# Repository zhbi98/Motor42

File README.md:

# Motor42

转速-扭矩特性步进电机运用普通的开环控制方式在低速和低负载的情况下可以保持较好的控制精度，但随着负载增大或转速度增加会发生丢步，另一个是转速-扭矩特性让步进电机无法在高转速下稳定工作。

## 特性

在低速状态下，步进电机的扭矩特性曲线通常为水平直线，能够提供较高的扭矩。在高速状态下，由于电感的影响，扭矩特性曲线呈指数下降，导致电机的负载能力显著降低。

> **最大扭矩：** 最大扭矩出现在中低转速范围，随着转速的提高，扭矩会逐渐下降。因为在高频率下，电流流动受到绕组电感的影响，导致电流无法达到稳定值，从而扭矩降低。
> 
> **启动扭矩与连续扭矩：** 启动扭矩指在启动时能够提供的最大扭矩，而连续扭矩则指电机持续运行时能够维持的扭矩。随着脉冲频率的增加，启动扭矩和连续扭矩都会下降。

## 闭环

闭环控制是在开环控制的基础上，增加了 **反馈检测环节**（例如在电机轴增加编码器），形成指令-执行-位置检测-修正的闭环逻辑。解决存在的丢步、偏差、抗干扰能力弱问题，还能提升系统和容错能力。

## FOC 控制

混合式步进电机与无刷电机的内在联系（结构定义相似性，工作原理相似性），所以可以用无刷电机 FOC 的驱动思想驱动步进电机。

结构方面：永磁转子+定子绕组的结构，定子方面：两者都有多相绕组（步进电机通常为两相，无刷电机通常为三相），转子方面：都采用永磁材料制造转子磁极，无刷设计：两者都没有电刷和机械换向器，依靠电子换向。

对于两相步进电机，虽然只有两个绕组，但通常两相绕组是正交的，从而可以简化步骤，省略我们的 clarke 变换，所以其余同样可以采用类似的思路进行一个电流环FOC控制。

    电流检测：对 AB 两相电流进行检测
    Park变换：将 AB 轴静止系转换为dq轴旋转坐标系
    PI调节器：对 Id 和 Iq 进行控制
    Invpark变换：讲 dq 轴转换为AB轴
    SVPWM调制: 输出占空比
    双 H桥驱动：驱动我们的步进电机

这些可以整合到一个驱动器中实现，如下图。这就是一体化集成步进电机闭环驱动器。板上集成磁编码器，具有速度，位置，电流闭环控制功能，适用于 3D 打印机，小型机械臂。

## 硬件

(1) 2 相逆变功率级：东芝凌耐压 50V，载流3.5A 的 PWM 斩波式双全桥电机驱动器，内置带低导通电阻的输出MOSFET（基于成本考虑可以选择其他的型号）。

(2) RS485 收发器：TI 德州仪器 SN75176B（基于成本考虑可以选择其他的型号）。

(3) CAN2.0B 收发器：NXP 恩智浦 High-speed CAN transceiver TJA1051（基于成本考虑可以选择其他的型号）。

(4) 磁编码器：MagnTek 麦歌恩 mt6816 单圈绝对式14位编码器，支持最高转速25Krpm。

(6) 主控 MUC 芯片：意法半导体 STM32F103。

## 关于打样

驱动器板 Motor42（PCB 采用?**4 层板**?设计）：[HardWare/kiacd_project](./HardWare/kiacd_project)

如果想自己修改 PCB 需要安装 KiCad（开源的 EDA 工具，也非常易学），官方下载地址： https://www.kicad.org/。

打样制作可以直接进入到下面这两个路径下：

把 Motor42 Gerber 文件夹 [HardWare/Gerber](./Docs/Motor42-PCB/) 压缩为 Motor42.zip，

把这个 .zip 给 PCB 制造厂即可（例如 JLC，**PCB 经过打样验证，可以放心使用**）。

**器件 BOM 目录**：[HardWare/ibom.html](./Docs/Motor42-BOM.csv)（PCB 没器件位号，按网页交互式 BOM 贴片）。

原理图 PDF 目录： [Docs/Motor42-SCH.csv](Docs/Motor42-SCH.pdf)

## 核心固件

固件主要包括几大功能模块：

- hal 驱动：板载的各种硬件驱动比如 USB、Tim、Can、Spi。
- utils 库：STM32 的 Flash 存储接口，Modbus 协议解析库，软定时器组件。
- drivers：ARM的CMSIS驱动，ST官方的HAL库。
- device：电机H桥驱动，编码器驱动和校准，电机控制核心代码，LED 驱动框架 LedMX 和按键驱动 MultiButton。
- main：上层 Can，Rs485 应用控制协议，用于控制同步电机状态/参数，以及用户设置参数保存功能。

## 编译下载

固件没有使用 ARM Keil 开发，而是先用 CMake 构建出 Makefile，然后再用 arm-gcc 编译（可以自己创建 F103 的 Keil 工程，把 Motor42 组织到 Keil 编译）。

Motor42 用的是 VSCode 搭配 OpenOCD 图形化下载调试，需要下载安装下列工具链：

MiniGW： https://sourceforge.net/projects/mingw-w64/files/

arm-gcc ：[Downloads | GNU Arm Embedded Toolchain Downloads – Arm Developer](https://developer.arm.com/downloads/-/gnu-rm)

openOCD：[Download OpenOCD for Windows](https://gnutoolchains.com/arm-eabi/openocd/)

CMake：[Download CMake](https://cmake.org/download/)

VSCode：[https://code.visualstudio.com/](https://code.visualstudio.com/)

> 安装后具体如何配置使用这些工具，篇幅较长不写在这里，我把具体配置使用方法写在这里：[工具链配置使用方法](https://blog.csdn.net/jf_52001760/article/details/126826393)。

**Motor42 编译步骤**：

把 cmake 脚本 CMakeLists.txt 的目录添加到 `1` 这里，如下图。

(2) 在 Firmware 目录下创建 build 目录，并指定到 `2` 这里。

(3) 点击 "Configure"，在弹出面板选择目标工程，如下图。

(5) 在 vscode 的命令行 `cd build` 进入`build/`目录，然后执行 make -j2 即可开始编译。

(6) 使用 openOCD 把 `.elf` 文件下载到 Motor42 硬件，下载方法同样参照 [工具链配置使用方法](https://blog.csdn.net/jf_52001760/article/details/126826393)（PCB 上预留了 SWD 调试接口同时支持固件下载）。

## 电机选型

电机可以在淘宝搜索购买，最好购买低相电阻步进电机（较好的电机的相电阻通常为 2-5 Ohm）。相电阻过高可能导致电机在静止时出现高频震动。

电机机身：34MM，出轴直径：5MM (D轴4.5MM)，出轴长度：22MM
静力矩：0.29 N.m，额定电流：1.5 A，电阻：3.0Ohm/相。

> 要实际测量电机相电阻（万用表接到对应相的两个端子测量），比如购买的步进电机在参数描述中标明的相电阻为 2.2 Ohm，实则实际测出的相电阻高达 29 Ohm
> 
> 

## 编码器安装

在电机轴上安装径向磁铁（用于磁编码器检测），磁铁尺寸?$d=8mm$，$h=2mm$，注意径向磁铁和轴同心度不要过度偏移，让后把驱动器板放到板支架中，用 M3.0 螺丝把驱动器和板定到电机尾部，磁铁与编码器的间隙大概为 $1mm$。

驱动板支架零件目录：[Model](./Model)，把 .step 文件给 3D 打印即可。

## Configuration

固件上已经调试好 Pid 参数，可以适配大多数42步进电机，默认情况下不需要再调试 Pid 电机也能正常工作。Pid 可以用 Can 指令调整（看Can协议部分的说明），方法如下：

- **Kp 的调整**：将 Kd，Ki 置 0，从零开始逐渐增加 Kp，直到系统出现震荡。然后逐渐减小Kp，直到系统不再震荡。Kp 的最终值通常在引起震荡的 Kp 值的 80%-90% 之间。

- **Kd 的调整**：在 Kp 调整稳定后，开始增加 Kd。如果系统在空载时仅需要 Kp，那么在负载情况下可能需要增加 Kd 来减少超调和震荡。

- **Ki 的调整**：如果系统在 Kp 和 Kd 的调整后仍然存在静态误差，可以尝试增加 Ki。但 Ki的值通常很小，需要细致地调整。

配置限制参数，限制参数再 /motor/control_config.h 文件定义，如下。

```c
/********************  硬件配置区  ********************/
#define _Current_Rated_Current  (3000)  /**< 额定电流(mA)*/
#define _Current_Cali_Current   (2000)  /**< 校准电流(mA)*/
/********************  运动参数配置区  ********************/
...
#define _Move_Rated_Speed           ((int32_t)(50 * Move_Pulse_NUM))    /**< (额定转速)(50转每秒)*/
#define _Move_Rated_UpAcc           ((int32_t)(1000 * Move_Pulse_NUM))  /**< (固件额定加速加速度)(1000r/ss)*/
#define _Move_Rated_DownAcc         ((int32_t)(1000 * Move_Pulse_NUM))  /**(固件额定减速加速度)(1000r/ss)*/
#define _Move_Rated_UpCurrentRate   ((int32_t)(20 * _Current_Rated_Current))    /**< (固件额定增流梯度)(20倍额定/s)*/
#define _Move_Rated_DownCurrentRate ((int32_t)(20 * _Current_Rated_Current))    /**< (固件额定减流梯度)(20倍额定/s)*/
```

用户设置在 /main/setup/setup.c 中定义，用户设置参数可以用 Can 指令设置（看Can协议部分的说明）设置后保存在 Flash 掉电保存。

```c
const _setup_t _setup_def = {
    ...
    .can_id = 0x01,
    .home_ofs = 0,
    ...
    .current_down_acc = 2 * 1000, /*(mA/s)*/
    .current_up_acc = 2 * 1000, /*(mA/s)*/
    .current_rated = 1000,
    .cali_current = 2000,
    ...
};
```

## 按键逻辑

(1) 启动停止闭环模式：按键 1 短按一次，启动或停止闭环模式，启动闭环模式的同时会进入默认的模式，例如位置闭环。

(2) 目标清 0：按键 2 短按一次，如果当前控制模式为速度模式，那么按下此时会将目标速度置为 0，位置模式，则将目标位置置为 0。

(3) 电机编码器校准：按键 1 长按两次，校准时电机会慢速正转一圈再反转一圈。

> 按下按键时 LED 跟随闪烁，以指示按键是否响应。

## 通信协议

驱动器支持 RS485+Modbus 和 CAN 协议。

### CAN 协议

一帧 CAN 报文只能传 8 个字节数据，和 11 位的标准 Std-Id，这里把 Std-Id 的低 7 位也用作数据，用来传控制指令字 CMD，控制协议定义如下：

Device Id 占用 4 位，CMD 占用 7 位，协议最多两个参数：参数 1 占用 4 个字节，参数 2 占用 4 个字节。

> 个别协议要两个参数，例如位置控制：设置目标位置和速度限制。

具体指令在[protocols/can_protocol.c](./Firmware/main/protocols/can_protocol.c) 这里定义，具体可以看这个文件，具体控制指令和控制方式查看 [Docs/Protocols](./Docs/Protocols) 目录下相应的协议文档，这里只截取部分。

### Rs485 协议

具体控制指令和控制方式查看 [Docs/Protocols](./Docs/Protocols) 目录下相应的协议文档，这里只截取部分。

## 震动问题

注意步进驱动器控制步进电机工作在位置环并要求静止在某个固定位置时可能会出现高频震动的问题。引起高频微弱震动的原因是由于在位置环控制模式下，驱动器为了让让电机接近指定位置而控制电机在齿槽间反复微调而产生震动。

> 这个现象排除驱动器的电路问题（比如焊接的电流采样电阻是否正确等等），磁编码器检测磁铁的安装同心度问题（通常同心度要求不是很高，确保不要过度偏移即可）那有极大的可能是步进电机的相电阻过大导致的，可以更换了其他电机进行测试。

如果更换电机测试后发现同一个闭环步进电机驱动器驱动一个步进电机工作在位置环保持静止时工作正常，而驱动另一个步进电机静止时出现高频震动，那可以肯定就是相电阻过高而导致的。出现震动现象的电机相电阻通常为 10-30 Ohm，而较好电机的相电阻通常为 2-5 Ohm。注意检查电机参数可能的虚标，例如购买的步进电机在参数描述中标明的相电阻为 2.2 Ohm，实则实际测出的相电阻高达 29 Ohm，所以电机出现震动现象和线圈相电阻是有一定关系的。

可以通过修改驱动器程序固件来修复这个问题，修改驱动输出部分，在最终 FOC 输出驱动电流部分添加一个系数即可，通过该系数来调节驱动器 FOC 的输出电流（当然调节电流参数会对最终的扭矩有略微的影响，但并不影响闭环精度），如下图。

## 控制带宽

电机控制速度/位置积分需要精确节拍，电机控制所有逻辑都是在定时器触发的中断中进行，我设置的中断函数频率较高，达到20KHz，可能会导致 main 主循环不执行。

> **20 kHz 中断**：TIM 每 50 μs 触发一次中断。

**电机控制逻辑较多：** 运行时间合计接近或超过 50 μs，会形成中断几乎连轴转、主循环几乎没机会跑”的情况（和芯片主频无关，只要中断内处理的时间超过中断周期时间就会导致 main 函数不执行）。

> 通过 SPI 阻塞读 MT6816，最多 3 次尝试 × 2 次 16bit 传输，再加 16 位奇偶校验循环。SPI 时钟为 9MHz，仅通信就可能 5-15μs。
> 
> 编码器处理、位置/速度估计、多种运行模式下的控制（DCE/PID/电流等）、运动规划、软目标更新、堵转/过载检测等就需要数十μs。

没有具体要求需要多少控制频率，控制制带宽越高，控制越平滑所以默认设定为 20KHz，若控制带宽允许，可把闭环控制改为 10 kHz 或 5 kHz，中断周期变为 100 μs / 200 μs。

> 这里 20 kHz 不是控制带宽的硬性要求，更多是裕量和步进分辨率。

修改控制频率同时改两处：
motion_planner.h 的  CONTROL_FREQUENCY 定义。
修改电机控制运行中断定时器的中断时间。

```c
/****************************************  控制器频率配置区  ****************************************/
#define CONTROL_FREQ_HZ   (20000)                     /**< 控制频率_hz*/
#define CONTROL_PERIOD_US (1000000 / CONTROL_FREQ_HZ) /**< 控制周期_us*/
```

### 评估控制带宽

(1) motor.cpp 涉及的一阶滤波：由 `等效时间常数由 >> 5`（约 32 个采样）决定。20 kHz 时：32 × 50us =1.6 ms 即控制带宽约 100 Hz。对很多应用来说 50 Hz 左右就足够。

(2) 位置/速度环 (DCE、PID 闭环带宽)：这是外环（位置环、速度环），一般做到几十到一两百 Hz 带宽就足够（位置/速度环 -3 dB 带宽）。 

> 常见经验：**采样率 ≥ 10～20 倍闭环带宽**。 
> 若你目标闭环带宽在 100～200 Hz，**5 kHz 已经够用，2 kHz 是底线**。

(3) FOC/电流指令：由 TB67H450 等驱动接收，5～10 kHz 更新电流给定对多数应用足够。

(4) 运动规划：用 CONTROL_FREQUENCY 做离散积分，频率高一点更平滑，但 5～10 kHz 通常足够平滑。

(5) 控制更新频率：下限约 2～5 kHz（再低速度估计和环路的相位裕量会变差）。推荐 5～10 kHz 在保证控制性能的同时，能给主循环留出明显时间。在需要 **极高步进率** 或 **尽量小的相位延迟** 时才必要 20 kHz。

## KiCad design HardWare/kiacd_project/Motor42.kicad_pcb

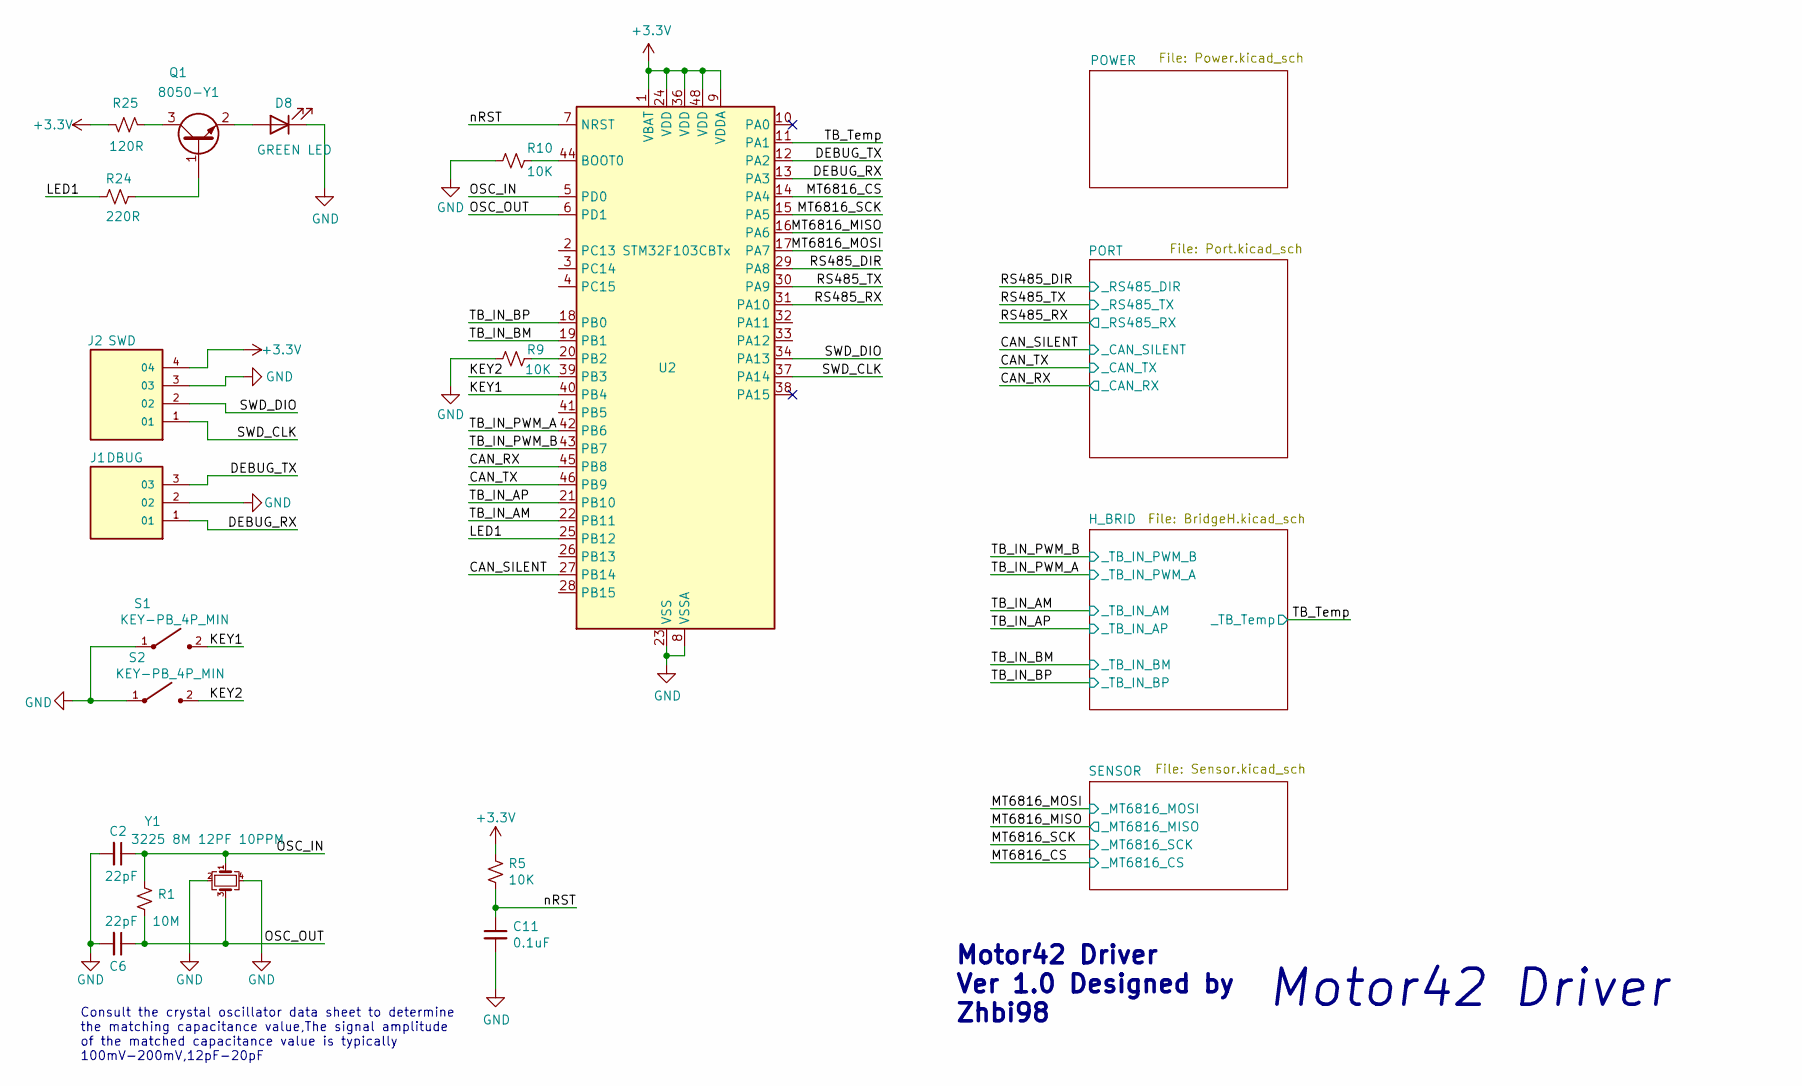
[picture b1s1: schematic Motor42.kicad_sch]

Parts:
C2, C6: 22pF; C_0603_1608Metric
C11: 0.1uF; C_0603_1608Metric
D8: GREEN LED; LED_0603_1608Metric
J1: DBUG; CONN-SMD_1x3P-P1.0-H_WAFER-SH1.0-3PWB
J2: SWD; CONN-SMD_1x4P-P1.0-H_WAFER-SH1.0-4PWB
Q1: 8050-Y1; SOT-23
R1: 10M; R_0603_1608Metric
R5, R9, R10: 10K; R_0603_1608Metric
R24: 220R; R_0603_1608Metric
R25: 120R; R_0603_1608Metric
S1, S2: KEY-PB_4P_MIN; KEY-SMD_2P_L4.0-W3.0-V_K2-1807SN-A3DW-06
U2: STM32F103CBTx; LQFP-48_7x7mm_P0.5mm
Y1: 3225 8M 12PF 10PPM; Crystal_SMD_3225-4Pin_3.2x2.5mm

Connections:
+3.3V: J2.4, R5.1, R25.1, U2.1 (VBAT), U2.9 (VDDA), U2.24 (VDD), U2.36 (VDD), U2.48 (VDD); also elsewhere on the board
/CAN_RX: U2.45 (PB8); also elsewhere on the board
/CAN_SILENT: U2.27 (PB14); also elsewhere on the board
/CAN_TX: U2.46 (PB9); also elsewhere on the board
/DEBUG_RX: J1.1, U2.13 (PA3)
/DEBUG_TX: J1.3, U2.12 (PA2)
/KEY1: S1.2, U2.40 (PB4)
/KEY2: S2.2, U2.39 (PB3)
/LED1: R24.2, U2.25 (PB12)
/MT6816_CS: U2.14 (PA4); also elsewhere on the board
/MT6816_MISO: U2.16 (PA6); also elsewhere on the board
/MT6816_MOSI: U2.17 (PA7); also elsewhere on the board
/MT6816_SCK: U2.15 (PA5); also elsewhere on the board
/OSC_IN: C2.1, R1.2, U2.5 (PD0), Y1.1
/OSC_OUT: C6.1, R1.1, U2.6 (PD1), Y1.3
/RS485_DIR: U2.29 (PA8); also elsewhere on the board
/RS485_RX: U2.31 (PA10); also elsewhere on the board
/RS485_TX: U2.30 (PA9); also elsewhere on the board
/SWD_CLK: J2.1, U2.37 (PA14)
/SWD_DIO: J2.2, U2.34 (PA13)
/TB_IN_AM: U2.22 (PB11); also elsewhere on the board
/TB_IN_AP: U2.21 (PB10); also elsewhere on the board
/TB_IN_BM: U2.19 (PB1); also elsewhere on the board
/TB_IN_BP: U2.18 (PB0); also elsewhere on the board
/TB_IN_PWM_A: U2.42 (PB6); also elsewhere on the board
/TB_IN_PWM_B: U2.43 (PB7); also elsewhere on the board
/TB_Temp: U2.11 (PA1); also elsewhere on the board
/nRST: C11.1, R5.2, U2.7 (NRST)
GND: C2.2, C6.2, C11.2, D8.1 (K), J1.2, J2.3, R9.2, R10.2, S1.1, S2.1, U2.8 (VSSA), U2.23 (VSS), U2.35 (VSS), U2.47 (VSS), Y1.2, Y1.4; also elsewhere on the board
unnamed: D8.2 (A), Q1.2 (E)
unnamed: Q1.1 (B), R24.1
unnamed: Q1.3 (C), R25.2
unnamed: R10.1, U2.44 (BOOT0)
unnamed: R9.1, U2.20 (PB2)

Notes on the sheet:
Motor42 Driver Ver 1.0 Designed by Zhbi98
Consult the crystal oscillator data sheet to determine the matching capacitance value,The signal amplitude of the matched capacitance value is typically 100mV-200mV,12pF-20pF
Motor42 Driver

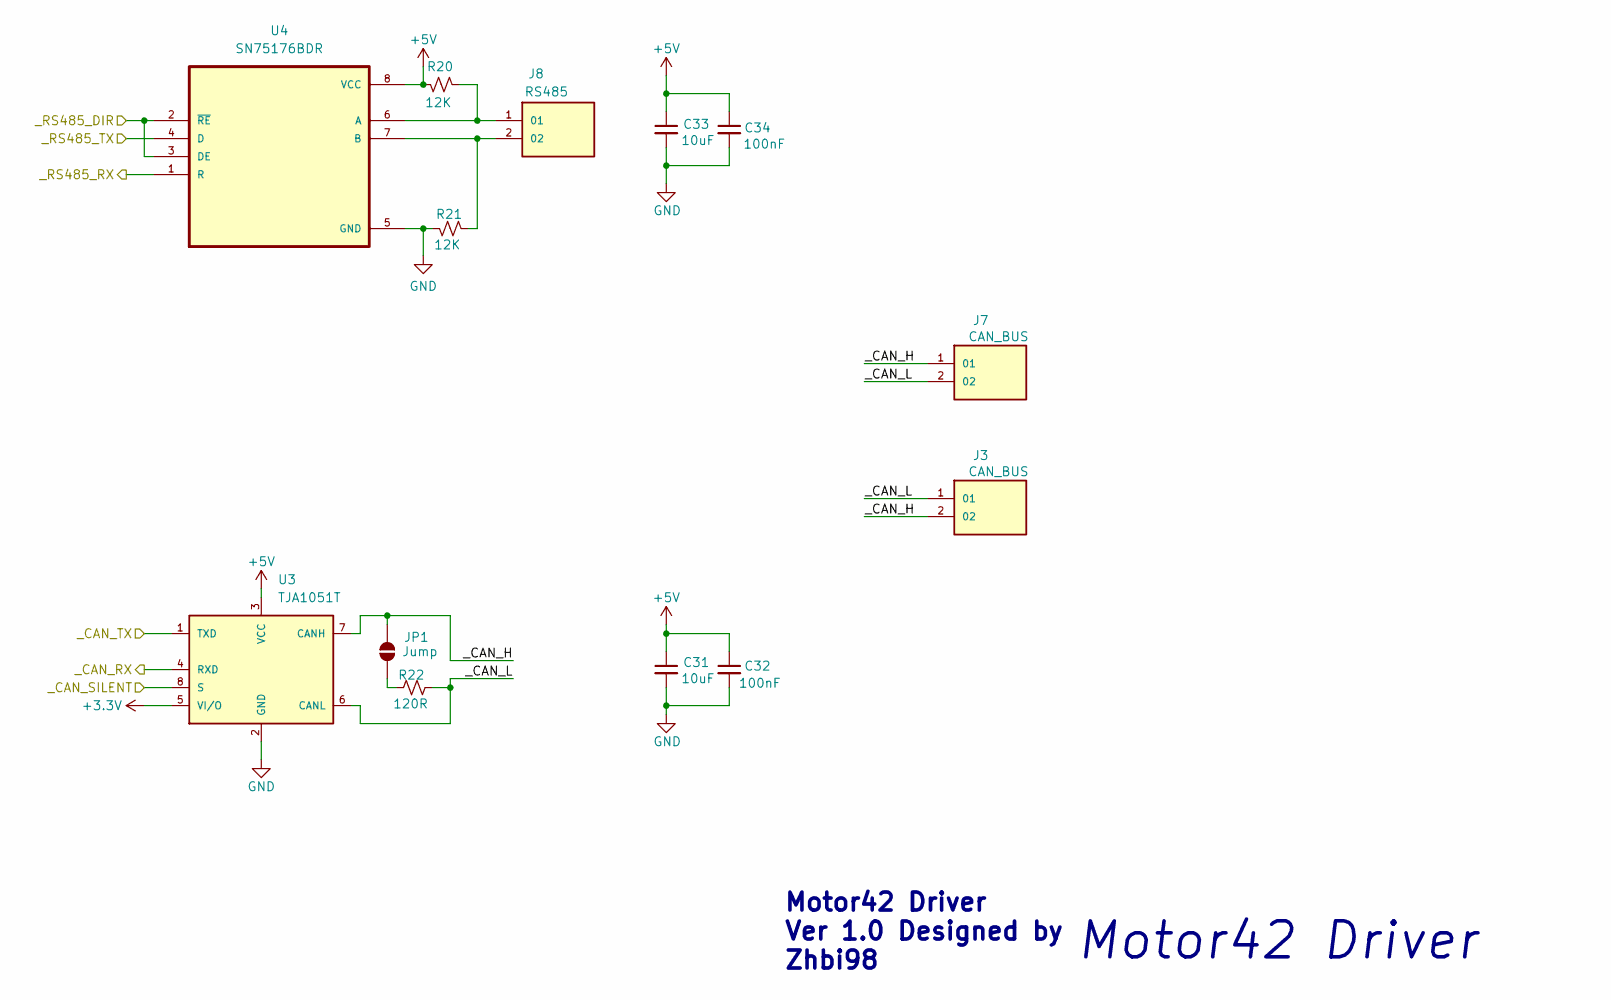
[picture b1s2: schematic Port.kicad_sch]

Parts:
C31, C33: 10uF; C_0603_1608Metric
C32, C34: 100nF; C_0603_1608Metric
J3, J7: CAN_BUS; CONN-SMD_1x2P-P1.0-H_WAFER-SH1.0-2PWB
J8: RS485; CONN-SMD_1x2P-P1.0-H_WAFER-SH1.0-2PWB
JP1: Jump; SolderJumper-2_P1.3mm_Open_RoundedPad1.0x1.5mm
R20, R21: 12K; R_0603_1608Metric
R22: 120R; R_0603_1608Metric
U3: TJA1051T; SOT96_L5.0-W4.0-P1.27_TJA1051
U4: SN75176BDR; SOIC-8_L5.0-W3.9-P1.27_SN75176BDR

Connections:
+3.3V: U3.5 (VI/O); also elsewhere on the board
+5V: C31.1, C32.1, C33.1, C34.1, R20.1, U3.3 (VCC), U4.8 (VCC); also elsewhere on the board
/CAN_RX: U3.4 (RXD); also elsewhere on the board
/CAN_SILENT: U3.8 (S); also elsewhere on the board
/CAN_TX: U3.1 (TXD); also elsewhere on the board
/PORT/_CAN_H: J3.2, J7.1, JP1.1 (A), U3.7 (CANH)
/PORT/_CAN_L: J3.1, J7.2, R22.2, U3.6 (CANL)
/RS485_DIR: U4.2 (~RE), U4.3 (DE); also elsewhere on the board
/RS485_RX: U4.1 (R); also elsewhere on the board
/RS485_TX: U4.4 (D); also elsewhere on the board
GND: C31.2, C32.2, C33.2, C34.2, R21.1, U3.2 (GND), U4.5 (GND); also elsewhere on the board
unnamed: J8.1, R20.2, U4.6 (A)
unnamed: J8.2, R21.2, U4.7 (B)
unnamed: JP1.2 (B), R22.1

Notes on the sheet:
Motor42 Driver
Motor42 Driver Ver 1.0 Designed by Zhbi98

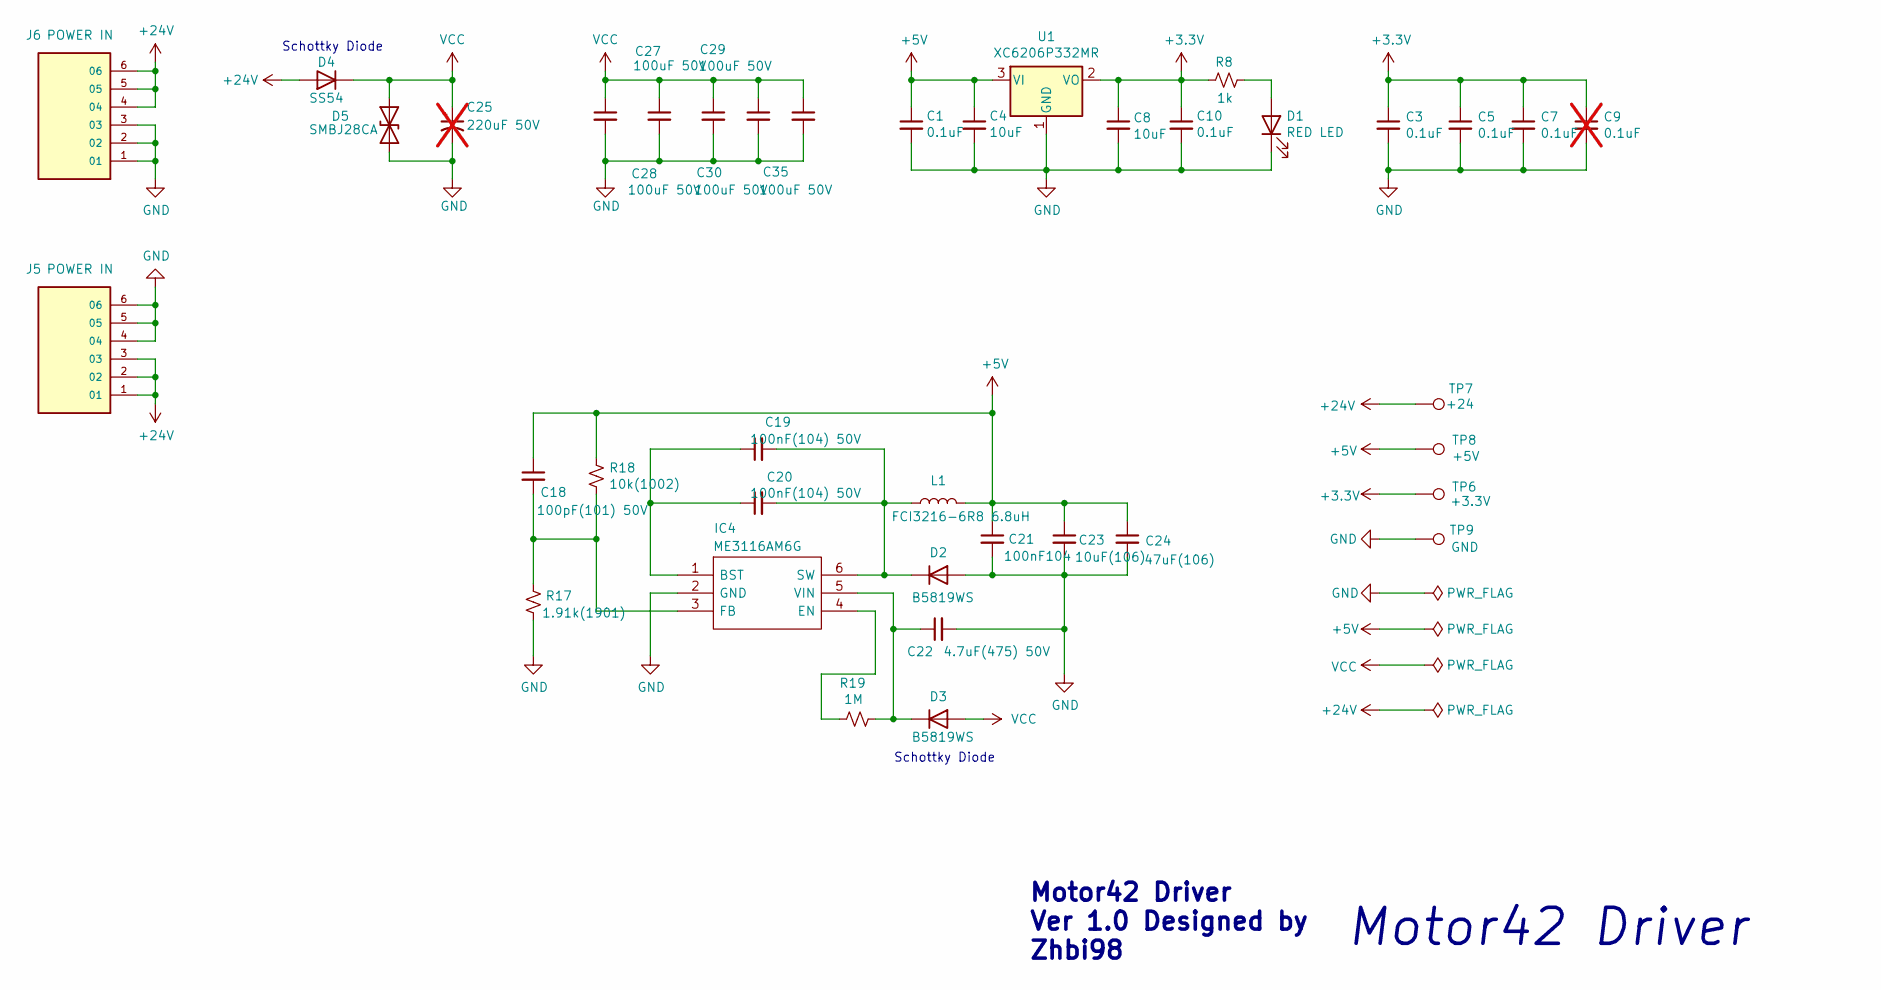
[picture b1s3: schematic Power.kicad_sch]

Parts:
C1, C3, C5, C7, C10: 0.1uF; C_0603_1608Metric
C4, C8: 10uF; C_0603_1608Metric
C9: 0.1uF; C_0603_1608Metric; not fitted
C18: 100pF(101) 50V; C_0603_1608Metric
C19, C20: 100nF(104) 50V; C_0603_1608Metric
C21: 100nF104; C_0603_1608Metric
C22: 4.7uF(475) 50V; C_1206_3216Metric
C23: 10uF(106); C_0603_1608Metric
C24: 47uF(106); C_0603_1608Metric
C25: 220uF 50V; CP_Elec_4x3; not fitted
C27, C28, C29, C30, C35: 100uF 50V; C_1206_3216Metric
D1: RED LED; LED_0603_1608Metric
D2, D3: B5819WS; D_0805_2012Metric
D4: SS54; D_SMA
D5: SMBJ28CA; D_SMB
IC4: ME3116AM6G; SOT-23-6_L2.7-W2.2-P0.95_ME3116AM6G; Manufacturer_Part_Number ME3116AM6G; Mouser Part Number 946-MP2451DTLFZ
J5, J6: POWER IN; CONN-SMD_1x6P-P2.0-H_WAFER-PH2.0-6PWB
L1: FCI3216-6R8 6.8uH; L_1206_3216Metric
R8: 1k; R_0603_1608Metric
R17: 1.91k(1901); R_0603_1608Metric
R18: 10k(1002); R_0603_1608Metric
R19: 1M; R_0603_1608Metric
TP6: +3.3V; TestPoint_Pad_D1.0mm
TP7: +24; TestPoint_Pad_D1.0mm
TP8: +5V; TestPoint_Pad_D1.0mm
TP9: GND; TestPoint_Pad_D1.0mm
U1: XC6206P332MR; SOT-23

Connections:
+3.3V: C3.1, C5.1, C7.1, C8.1, C9.1, C10.1, R8.1, TP6.1, U1.2 (VO); also elsewhere on the board
+5V: C1.1, C4.1, C18.1, C21.1, C23.1, C24.1, L1.2, R18.1, TP8.1, U1.3 (VI); also elsewhere on the board
+24V: D4.2 (A), J5.1, J5.2, J5.3, J6.4, J6.5, J6.6, TP7.1
GND: C1.2, C3.2, C4.2, C5.2, C7.2, C8.2, C9.2, C10.2, C21.2, C22.2, C23.2, C24.2, C25.2, C27.2, C28.2, C29.2, C30.2, C35.2, D1.1 (K), D2.2 (A), D5.1 (A1), IC4.2 (GND), J5.4, J5.5, J5.6, J6.1, J6.2, J6.3, R17.2, TP9.1, U1.1 (GND); also elsewhere on the board
unnamed: D1.2 (A), R8.2
unnamed: C19.2, C20.2, D2.1 (K), IC4.6 (SW), L1.1
unnamed: C22.1, D3.1 (K), IC4.5 (VIN), R19.2
unnamed: C19.1, C20.1, IC4.1 (BST)
unnamed: IC4.4 (EN), R19.1
unnamed: C18.2, IC4.3 (FB), R17.1, R18.2
VCC: C25.1, C27.1, C28.1, C29.1, C30.1, C35.1, D3.2 (A), D4.1 (K), D5.2 (A2); also elsewhere on the board

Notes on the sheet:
Schottky Diode
Motor42 Driver Ver 1.0 Designed by Zhbi98
Motor42 Driver

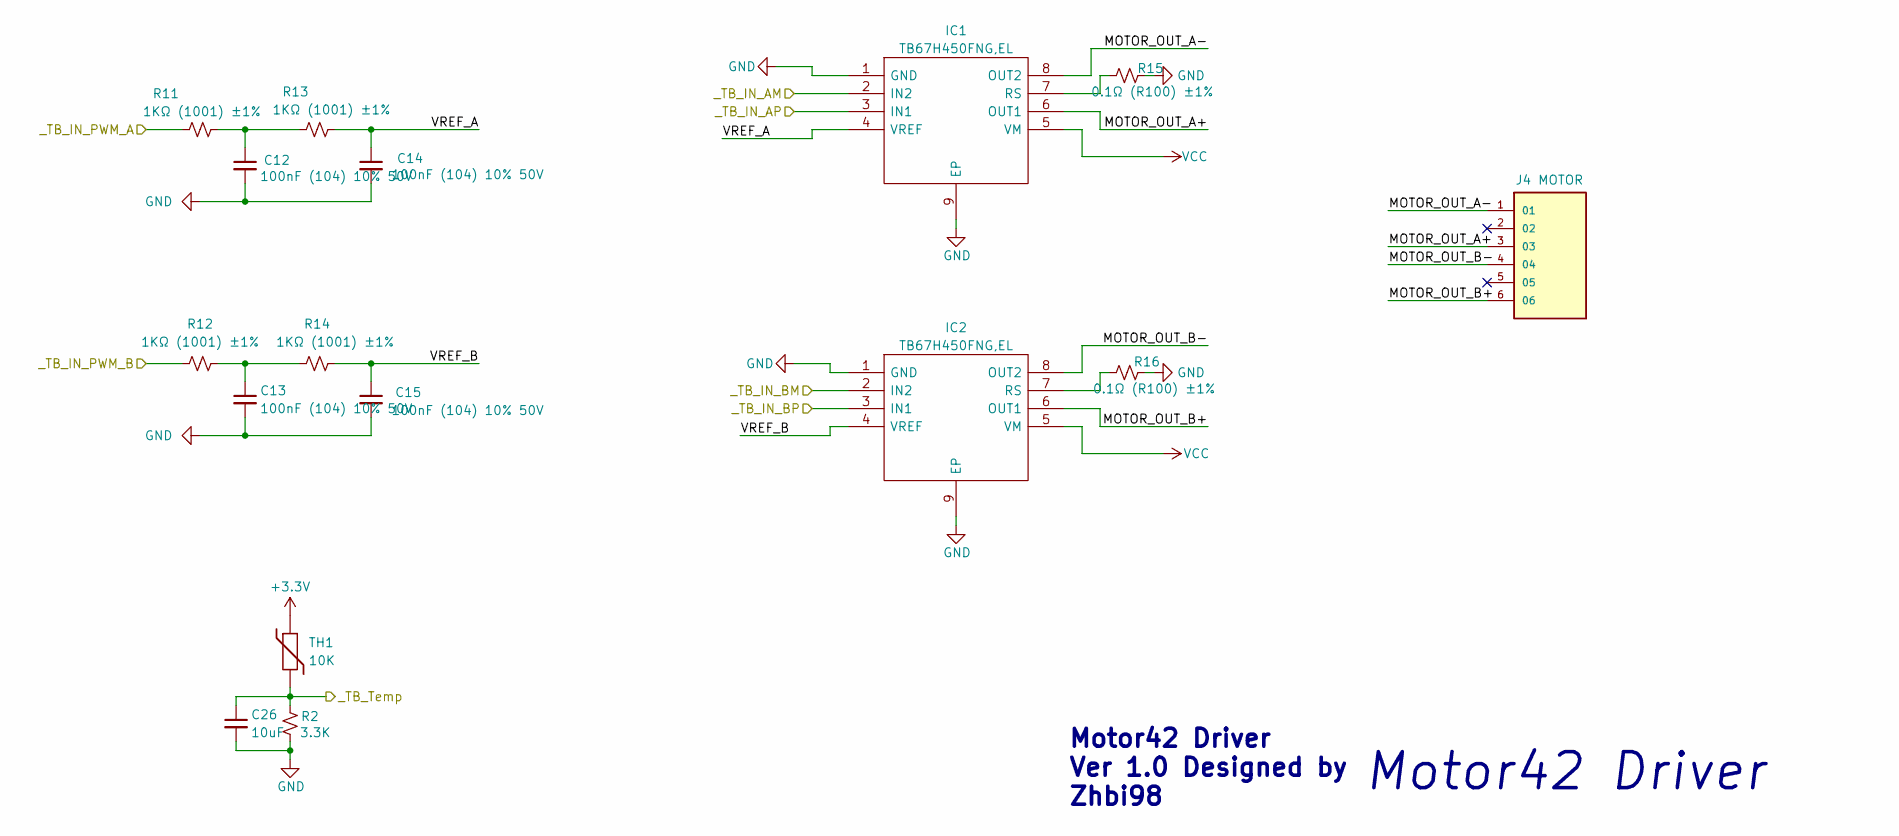
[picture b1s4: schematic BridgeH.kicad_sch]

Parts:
C12, C13, C14, C15: 100nF (104) 10% 50V; C_0603_1608Metric
C26: 10uF; C_0603_1608Metric
IC1, IC2: TB67H450FNG,EL; SOIC-8_L4.8-W5.8-P1.27_TB67H450FNG; Manufacturer_Part_Number TB67H450FNG,EL; Mouser Part Number 757-TB67H450FNGEL
J4: MOTOR; CONN-SMD_1x6P-P2.0-H_WAFER-PH2.0-6PWB
R2: 3.3K; R_0603_1608Metric
R11, R12, R13, R14: 1KΩ (1001) ±1%; R_0603_1608Metric
R15, R16: 0.1Ω (R100) ±1%; R_1206_3216Metric
TH1: 10K; R_0603_1608Metric

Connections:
+3.3V: TH1.1; also elsewhere on the board
/H_BRID/MOTOR_OUT_A+: IC1.6 (OUT1), J4.3
/H_BRID/MOTOR_OUT_A-: IC1.8 (OUT2), J4.1
/H_BRID/MOTOR_OUT_B+: IC2.6 (OUT1), J4.6
/H_BRID/MOTOR_OUT_B-: IC2.8 (OUT2), J4.4
/H_BRID/VREF_A: C14.1, IC1.4 (VREF), R13.2
/H_BRID/VREF_B: C15.1, IC2.4 (VREF), R14.2
/TB_IN_AM: IC1.2 (IN2); also elsewhere on the board
/TB_IN_AP: IC1.3 (IN1); also elsewhere on the board
/TB_IN_BM: IC2.2 (IN2); also elsewhere on the board
/TB_IN_BP: IC2.3 (IN1); also elsewhere on the board
/TB_IN_PWM_A: R11.1; also elsewhere on the board
/TB_IN_PWM_B: R12.1; also elsewhere on the board
/TB_Temp: C26.1, R2.2, TH1.2; also elsewhere on the board
GND: C12.2, C13.2, C14.2, C15.2, C26.2, IC1.1 (GND), IC1.9 (EP), IC2.1 (GND), IC2.9 (EP), R2.1, R15.2, R16.2; also elsewhere on the board
unnamed: C12.1, R11.2, R13.1
unnamed: C13.1, R12.2, R14.1
unnamed: IC1.7 (RS), R15.1
unnamed: IC2.7 (RS), R16.1
VCC: IC1.5 (VM), IC2.5 (VM); also elsewhere on the board

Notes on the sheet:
Motor42 Driver Ver 1.0 Designed by Zhbi98
Motor42 Driver

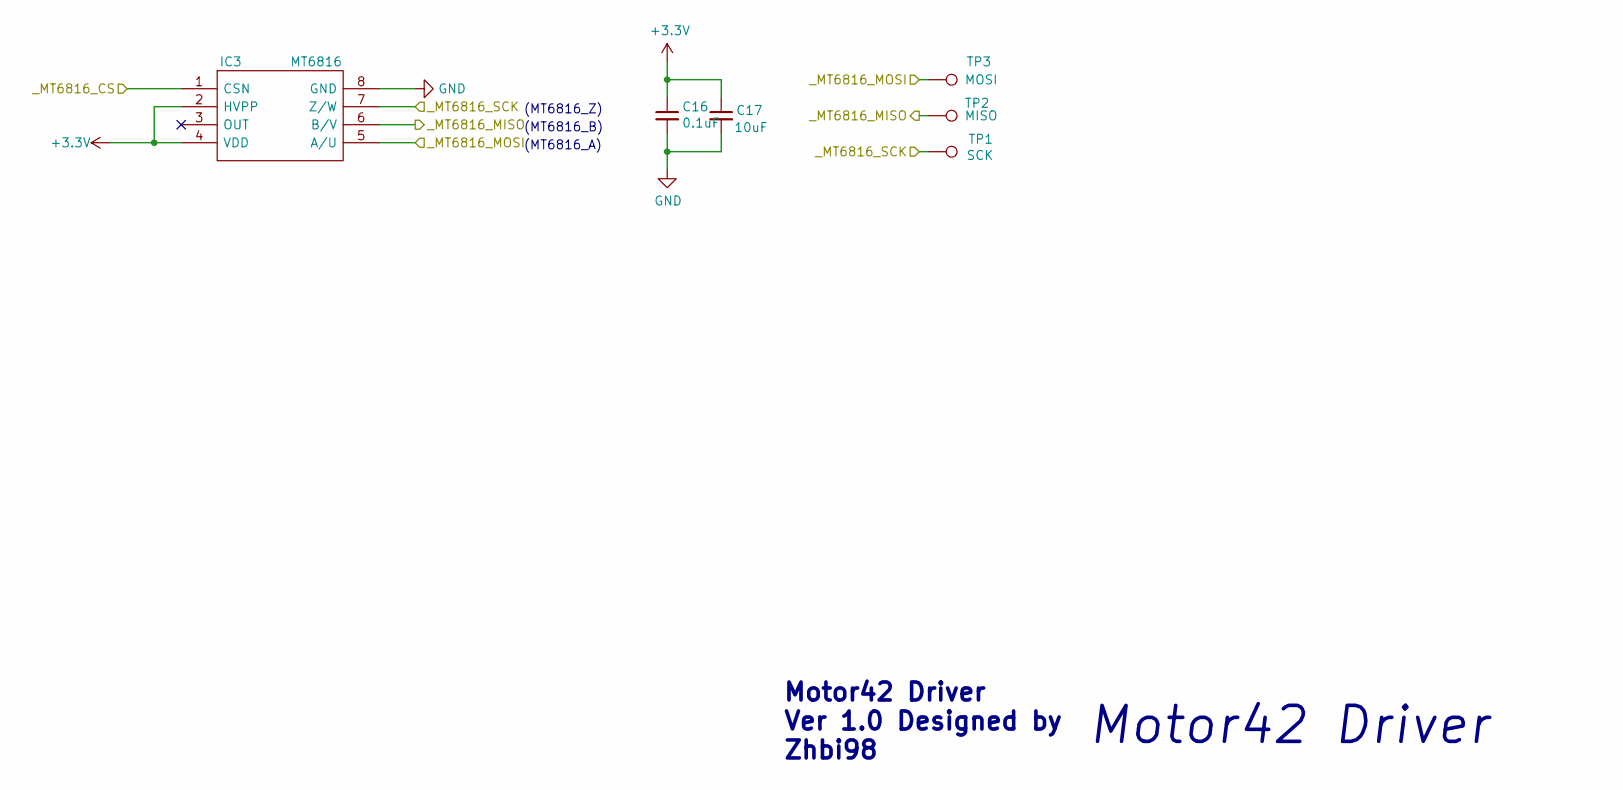
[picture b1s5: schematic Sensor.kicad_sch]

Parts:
C16: 0.1uF; C_0603_1608Metric
C17: 10uF; C_0603_1608Metric
IC3: MT6816; SOIC-8_L4.7-W5.8-P1.27_MT6816; Manufacturer_Part_Number MT6816
TP1: SCK; TestPoint_Pad_D1.0mm
TP2: MISO; TestPoint_Pad_D1.0mm
TP3: MOSI; TestPoint_Pad_D1.0mm

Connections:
+3.3V: C16.1, C17.1, IC3.2 (HVPP), IC3.4 (VDD); also elsewhere on the board
/MT6816_CS: IC3.1 (CSN); also elsewhere on the board
/MT6816_MISO: IC3.6 (B/V), TP2.1; also elsewhere on the board
/MT6816_MOSI: IC3.5 (A/U), TP3.1; also elsewhere on the board
/MT6816_SCK: IC3.7 (Z/W), TP1.1; also elsewhere on the board
GND: C16.2, C17.2, IC3.8 (GND); also elsewhere on the board

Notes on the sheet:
(MT6816_B)
(MT6816_A)
Motor42 Driver
Motor42 Driver Ver 1.0 Designed by Zhbi98
(MT6816_Z)

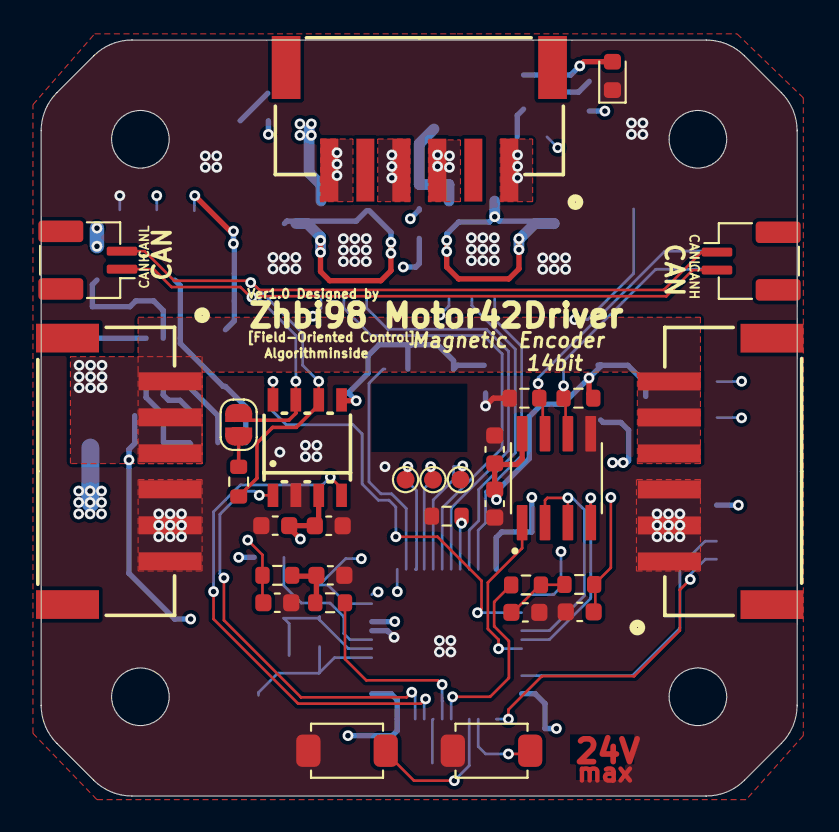
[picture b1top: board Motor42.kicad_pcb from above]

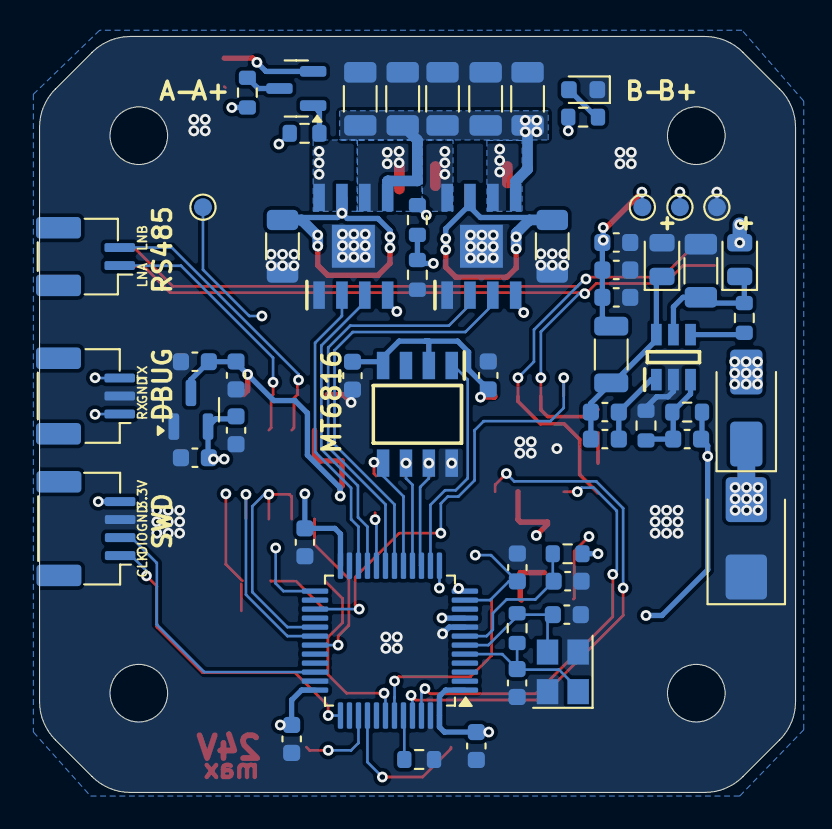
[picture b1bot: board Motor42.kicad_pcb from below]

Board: 4 copper layers, 42.0 x 42.0 mm, 89 parts (59 on the bottom side), 58 nets.

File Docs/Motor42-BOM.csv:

"Reference","Value","Datasheet","Footprint","Qty","DNP"
"C1,C3,C5,C7,C10,C11,C16","0.1uF","~","Capacitor_SMD:C_0603_1608Metric","7",""
"C2,C6","22pF","~","Capacitor_SMD:C_0603_1608Metric","2",""
"C4,C8,C17,C26,C31,C33","10uF","~","Capacitor_SMD:C_0603_1608Metric","6",""
"C12,C13,C14,C15","100nF (104) 10% 50V","~","Capacitor_SMD:C_0603_1608Metric","4",""
"C18","100pF(101) 50V","~","Capacitor_SMD:C_0603_1608Metric","1",""
"C19,C20","100nF(104) 50V","~","Capacitor_SMD:C_0603_1608Metric","2",""
"C21","100nF104","~","Capacitor_SMD:C_0603_1608Metric","1",""
"C22","4.7uF(475) 50V","~","Capacitor_SMD:C_1206_3216Metric","1",""
"C23","10uF(106)","~","Capacitor_SMD:C_0603_1608Metric","1",""
"C24","47uF(106)","~","Capacitor_SMD:C_0603_1608Metric","1",""
"C27,C28,C29,C30,C35","100uF 50V","~","Capacitor_SMD:C_1206_3216Metric","5",""
"C32,C34","100nF","~","Capacitor_SMD:C_0603_1608Metric","2",""
"D1","RED LED","~","LED_SMD:LED_0603_1608Metric","1",""
"D2,D3","B5819WS","http://www.vishay.com/docs/85622/1n914.pdf","Diode_SMD:D_0805_2012Metric","2",""
"D4","SS54","http://www.vishay.com/docs/85622/1n914.pdf","Diode_SMD:D_SMA","1",""
"D5","SMBJ28CA","https://www.vishay.com/docs/88301/15ke.pdf","Diode_SMD:D_SMB","1",""
"D8","GREEN LED","~","LED_SMD:LED_0603_1608Metric","1",""
"IC1,IC2","TB67H450FNG,EL","http://toshiba.semicon-storage.com/info/docget.jsp?did=65346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","3rd_Driver_Motor:SOIC-8_L4.8-W5.8-P1.27_TB67H450FNG","2",""
"IC3","MT6816","http://www.magntek.com.cn/upload/MT6816_Rev.2.0.pdf","3rd_Sensor_Encoder:SOIC-8_L4.7-W5.8-P1.27_MT6816","1",""
"IC4","ME3116AM6G","https://componentsearchengine.com/Datasheets/1/ME3116AM6G.pdf","3rd_Converter_DCDC:SOT-23-6_L2.7-W2.2-P0.95_ME3116AM6G","1",""
"J1","DBUG","","3rd_Connector_JST_SMD:CONN-SMD_1x3P-P1.0-H_WAFER-SH1.0-3PWB","1",""
"J2","SWD","","3rd_Connector_JST_SMD:CONN-SMD_1x4P-P1.0-H_WAFER-SH1.0-4PWB","1",""
"J3,J7","CAN_BUS","","3rd_Connector_JST_SMD:CONN-SMD_1x2P-P1.0-H_WAFER-SH1.0-2PWB","2",""
"J4","MOTOR","","3rd_Connector_JST_SMD:CONN-SMD_1x6P-P2.0-H_WAFER-PH2.0-6PWB","1",""
"J5,J6","POWER IN","","3rd_Connector_JST_SMD:CONN-SMD_1x6P-P2.0-H_WAFER-PH2.0-6PWB","2",""
"J8","RS485","","3rd_Connector_JST_SMD:CONN-SMD_1x2P-P1.0-H_WAFER-SH1.0-2PWB","1",""
"JP1","Jump","~","Jumper:SolderJumper-2_P1.3mm_Open_RoundedPad1.0x1.5mm","1",""
"L1","FCI3216-6R8  6.8uH","~","Inductor_SMD:L_1206_3216Metric","1",""
"Q1","8050-Y1","~","Package_TO_SOT_SMD:SOT-23","1",""
"R1","10M","~","Resistor_SMD:R_0603_1608Metric","1",""
"R2","3.3K","~","Resistor_SMD:R_0603_1608Metric","1",""
"R5,R9,R10,TH1","10K","~","Resistor_SMD:R_0603_1608Metric","4",""
"R8","1k","~","Resistor_SMD:R_0603_1608Metric","1",""
"R11,R12,R13,R14","1KΩ (1001) ±1%","~","Resistor_SMD:R_0603_1608Metric","4",""
"R15,R16","0.1Ω (R100) ±1%","~","Resistor_SMD:R_1206_3216Metric","2",""
"R17","1.91k(1901)","~","Resistor_SMD:R_0603_1608Metric","1",""
"R18","10k(1002)","~","Resistor_SMD:R_0603_1608Metric","1",""
"R19","1M","~","Resistor_SMD:R_0603_1608Metric","1",""
"R20,R21","12K","~","Resistor_SMD:R_0603_1608Metric","2",""
"R22,R25","120R","~","Resistor_SMD:R_0603_1608Metric","2",""
"R24","220R","~","Resistor_SMD:R_0603_1608Metric","1",""
"S1,S2","KEY-PB_4P_MIN","","3rd_Button_Switch_SMD:KEY-SMD_2P_L4.0-W3.0-V_K2-1807SN-A3DW-06","2",""
"TP1","SCK","~","TestPoint:TestPoint_Pad_D1.0mm","1",""
"TP2","MISO","~","TestPoint:TestPoint_Pad_D1.0mm","1",""
"TP3","MOSI","~","TestPoint:TestPoint_Pad_D1.0mm","1",""
"TP6","+3.3V","~","TestPoint:TestPoint_Pad_D1.0mm","1",""
"TP7","+24","~","TestPoint:TestPoint_Pad_D1.0mm","1",""
"TP8","+5V","~","TestPoint:TestPoint_Pad_D1.0mm","1",""
"TP9","GND","~","TestPoint:TestPoint_Pad_D1.0mm","1",""
"U1","XC6206P332MR","https://www.torexsemi.com/file/xc6206/XC6206.pdf","Package_TO_SOT_SMD:SOT-23","1",""
"U2","STM32F103CBTx","https://www.st.com/resource/en/datasheet/stm32f103cb.pdf","Package_QFP:LQFP-48_7x7mm_P0.5mm","1",""
"U3","TJA1051T","","3rd_Interface_CAN:SOT96_L5.0-W4.0-P1.27_TJA1051","1",""
"U4","SN75176BDR","","3rd_Interface_UART:SOIC-8_L5.0-W3.9-P1.27_SN75176BDR","1",""
"Y1","3225 8M 12PF 10PPM","~","Crystal:Crystal_SMD_3225-4Pin_3.2x2.5mm","1",""

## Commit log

2025-02-23 更新LED及按键驱动程序
2025-02-23 修改CMakeLists.txt构建目录
2025-02-24 更新文件之间引用关系
2025-02-26 更新 Signal 组件
2025-03-01 添加电机按键控制，与指示灯信号
2025-03-07 添加电机模式按键控制
2025-03-08 添加 CAN 控制指令，增加控制参数请求接口
2025-03-09 用户设置参数存储功能
2025-03-10 完善控制指令，增加磁编码器零点偏移设置
2025-03-11 调整电机可变参数配置与初始化方式
2025-03-13 添加过温保护 ADC 驱动
2025-03-15 解决闭环控制高频中断导致主循环不运行问题(按键, LED不响应)，适配新PCB调整 GPIO 分配
2025-03-16 使用软件定时器解决闭环控制高频中断导致主循环不运行，CAN 中断低优先级中断滞后问题(以及按键, LED不响应)
2025-03-19 复杂计算部分添加注释
2025-03-19 添加硬件设计文档
2025-03-20 添加电机过热检测和保护
2025-03-27 更新震动问题的原因和解决办法说明
2025-04-09 添加 RS485 控制协议
2025-04-14 位置环控制时调节到达目标位置的额定速度和时间，新额定速度，过程时间未生效问题
2025-04-18 添加控制协议表格
2025-04-19 更新 README,添加零件，添加协议文档
2025-07-20 Can not set the acceleration, otherwise the mode switching speed can not be limited in time.
    Can not set the acceleration, otherwise the mode switching speed can not be limited in time.
2025-08-12 增加设备串口输出流__fputs接口
2026-03-06 完善README说明文档
